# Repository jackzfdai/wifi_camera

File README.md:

# wifi_camera
ESP32 based connected camera, includes PCB files, ESP32 code, and a Python server for receiving the video stream.

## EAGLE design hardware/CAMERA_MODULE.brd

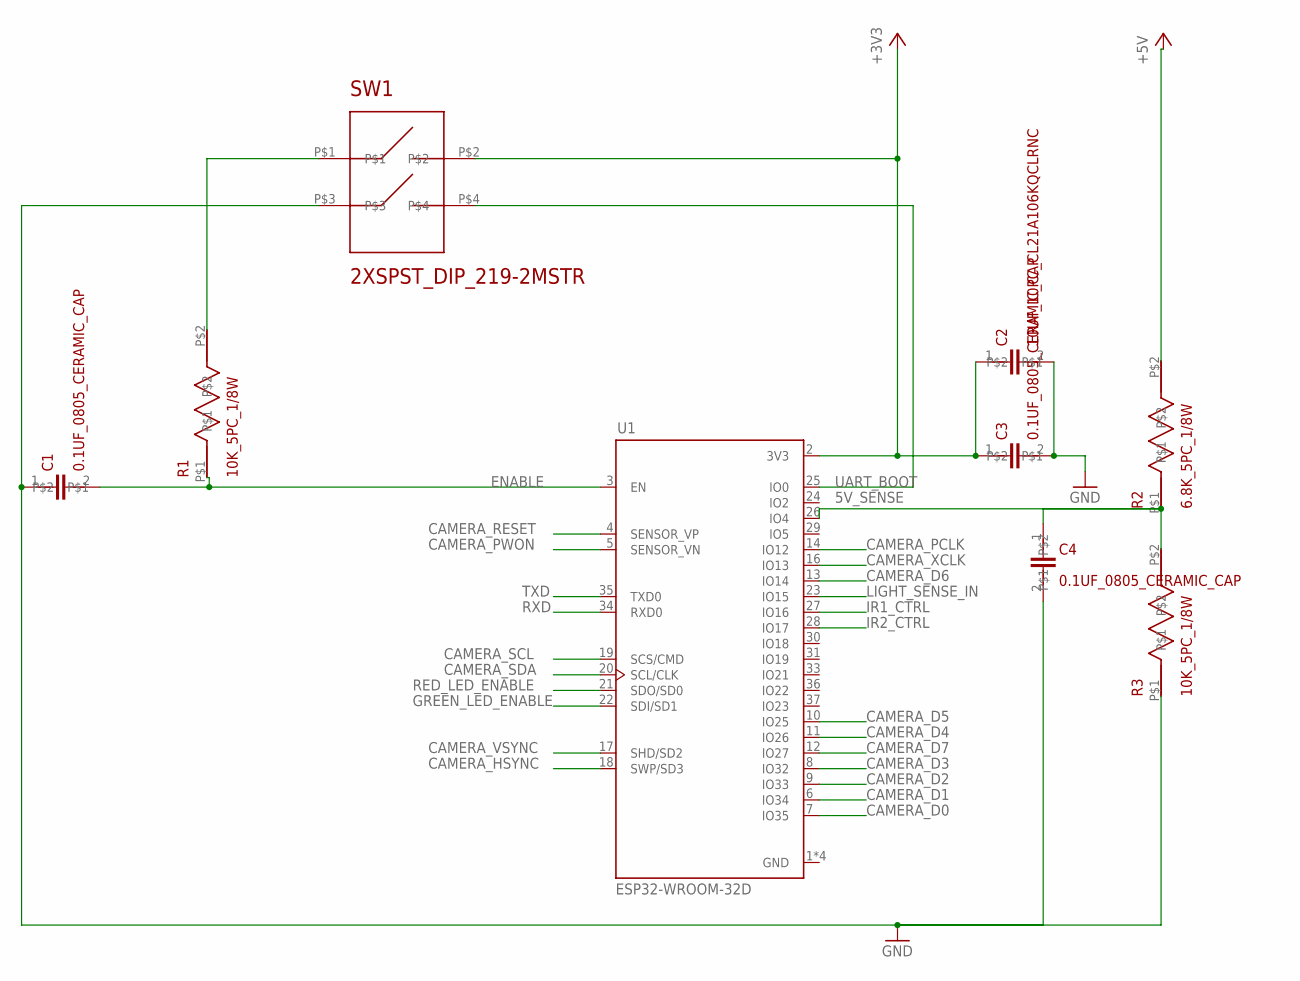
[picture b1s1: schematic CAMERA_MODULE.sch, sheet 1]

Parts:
C1, C3, C4: 0.1UF_0805_CERAMIC_CAP; C0805K
C2: 10UF_10PC_CL21A106KQCLRNC; C0805K
R1, R3: 10K_5PC_1/8W; 0805_1
R2: 6.8K_5PC_1/8W; 0805_1
SW1: 2XSPST_DIP_219-2MSTR; 2XSPST
U1: ESP32-WROOM-32D; MODULE_ESP32-WROOM-32D

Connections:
5V_SENSE: C4.1, R2.P$1, R3.P$2, U1.26 (IO4)
+3V3: C2.1, C3.1, SW1.P$2, U1.2 (3V3); also elsewhere on the board
+5V: R2.P$2; also elsewhere on the board
CAMERA_D0: U1.7 (IO35); also elsewhere on the board
CAMERA_D1: U1.6 (IO34); also elsewhere on the board
CAMERA_D2: U1.9 (IO33); also elsewhere on the board
CAMERA_D3: U1.8 (IO32); also elsewhere on the board
CAMERA_D4: U1.11 (IO26); also elsewhere on the board
CAMERA_D5: U1.10 (IO25); also elsewhere on the board
CAMERA_D6: U1.13 (IO14); also elsewhere on the board
CAMERA_D7: U1.12 (IO27); also elsewhere on the board
CAMERA_HSYNC: U1.18 (SWP/SD3); also elsewhere on the board
CAMERA_PCLK: U1.14 (IO12); also elsewhere on the board
CAMERA_PWON: U1.5 (SENSOR_VN); also elsewhere on the board
CAMERA_RESET: U1.4 (SENSOR_VP); also elsewhere on the board
CAMERA_SCL: U1.19 (SCS/CMD); also elsewhere on the board
CAMERA_SDA: U1.20 (SCL/CLK); also elsewhere on the board
CAMERA_VSYNC: U1.17 (SHD/SD2); also elsewhere on the board
CAMERA_XCLK: U1.16 (IO13); also elsewhere on the board
ENABLE: C1.2, R1.P$1, U1.3 (EN)
GND: C1.1, C2.2, C3.2, C4.2, R3.P$1, SW1.P$3, U1.1 (GND), U1.15 (GND), U1.38 (GND), U1.39 (GND); also elsewhere on the board
GREEN_LED_ENABLE: U1.22 (SDI/SD1); also elsewhere on the board
IR1_CTRL: U1.27 (IO16); also elsewhere on the board
IR2_CTRL: U1.28 (IO17); also elsewhere on the board
LIGHT_SENSE_IN: U1.23 (IO15); also elsewhere on the board
unnamed: R1.P$2, SW1.P$1
RED_LED_ENABLE: U1.21 (SDO/SD0); also elsewhere on the board
RXD: U1.34 (RXD0); also elsewhere on the board
TXD: U1.35 (TXD0); also elsewhere on the board
UART_BOOT: SW1.P$4, U1.25 (IO0)

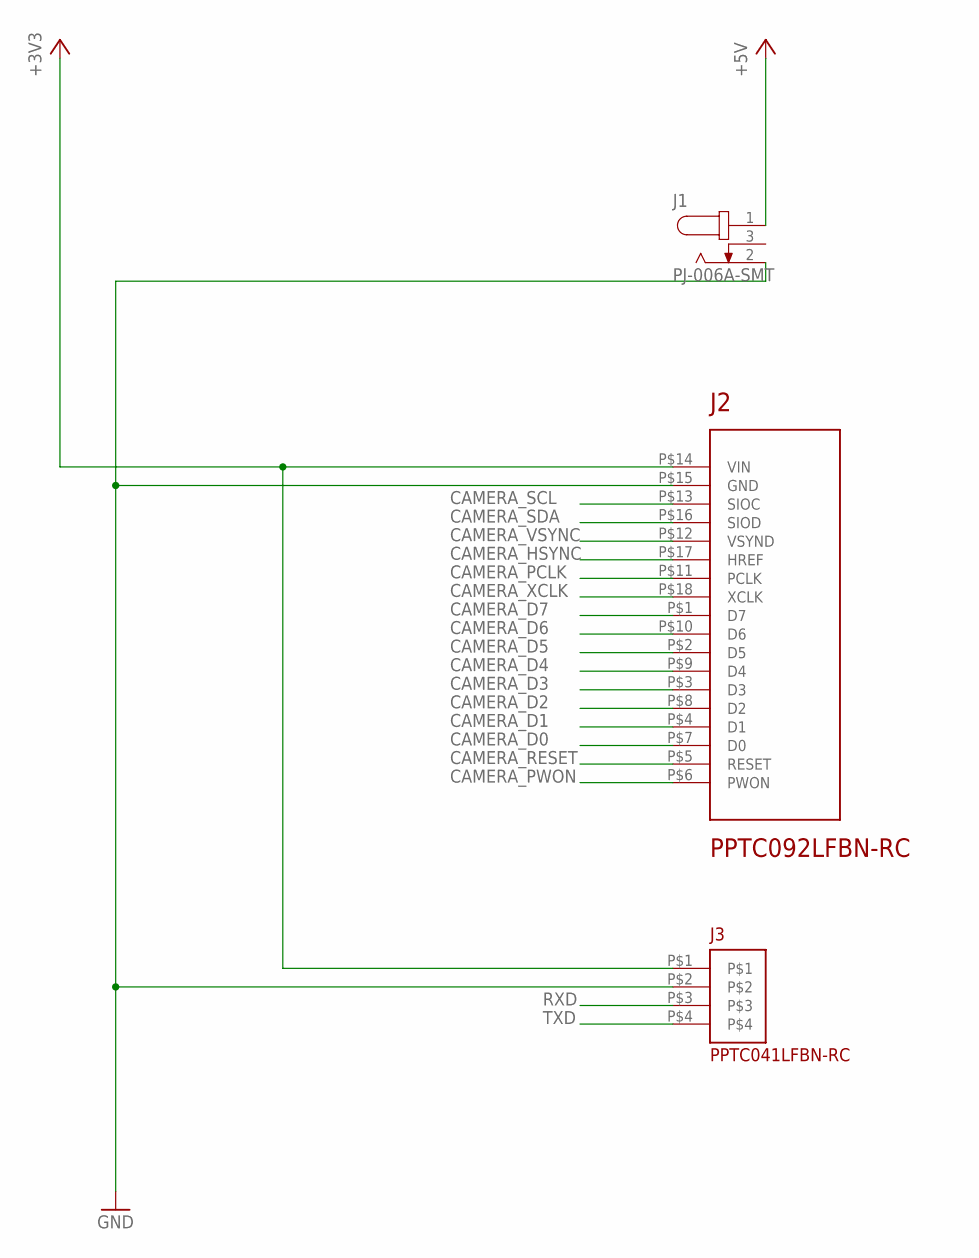
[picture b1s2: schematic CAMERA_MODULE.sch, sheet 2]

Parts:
J1: PJ-006A-SMT; CUI_PJ-006A-SMT
J2: PPTC092LFBN-RC; 2X9_0.1INCH
J3: PPTC041LFBN-RC; 1X4_0.1INCH

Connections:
+3V3: J2.P$14 (VIN), J3.P$1; also elsewhere on the board
+5V: J1.1; also elsewhere on the board
CAMERA_D0: J2.P$7 (D0); also elsewhere on the board
CAMERA_D1: J2.P$4 (D1); also elsewhere on the board
CAMERA_D2: J2.P$8 (D2); also elsewhere on the board
CAMERA_D3: J2.P$3 (D3); also elsewhere on the board
CAMERA_D4: J2.P$9 (D4); also elsewhere on the board
CAMERA_D5: J2.P$2 (D5); also elsewhere on the board
CAMERA_D6: J2.P$10 (D6); also elsewhere on the board
CAMERA_D7: J2.P$1 (D7); also elsewhere on the board
CAMERA_HSYNC: J2.P$17 (HREF); also elsewhere on the board
CAMERA_PCLK: J2.P$11 (PCLK); also elsewhere on the board
CAMERA_PWON: J2.P$6 (PWON); also elsewhere on the board
CAMERA_RESET: J2.P$5 (RESET); also elsewhere on the board
CAMERA_SCL: J2.P$13 (SIOC); also elsewhere on the board
CAMERA_SDA: J2.P$16 (SIOD); also elsewhere on the board
CAMERA_VSYNC: J2.P$12 (VSYND); also elsewhere on the board
CAMERA_XCLK: J2.P$18 (XCLK); also elsewhere on the board
GND: J1.2, J2.P$15 (GND), J3.P$2; also elsewhere on the board
RXD: J3.P$3; also elsewhere on the board
TXD: J3.P$4; also elsewhere on the board

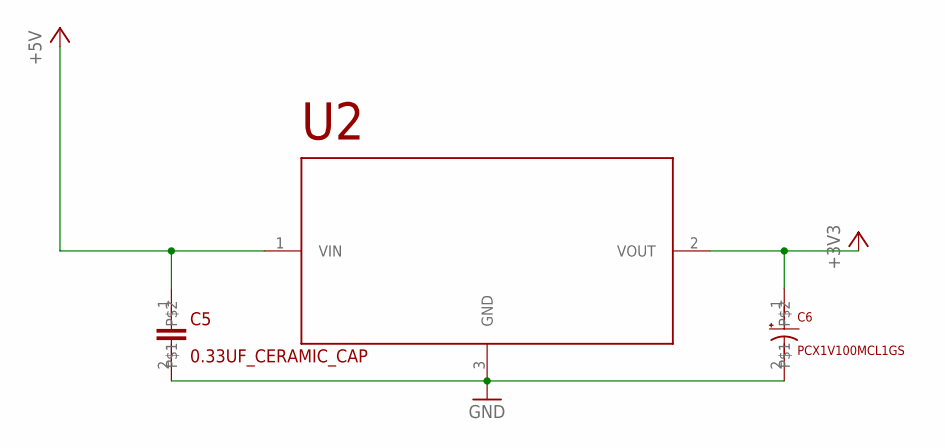
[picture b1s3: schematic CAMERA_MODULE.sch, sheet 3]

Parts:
C5: 0.33UF_CERAMIC_CAP; CAPC3216X110N
C6: PCX1V100MCL1GS; CAPAE660X600N
U2: LD29150DT33R; VREG_L7805CDT-TR

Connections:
+3V3: C6.1, U2.2 (VOUT); also elsewhere on the board
+5V: C5.1, U2.1 (VIN); also elsewhere on the board
GND: C5.2, C6.2, U2.3 (GND); also elsewhere on the board

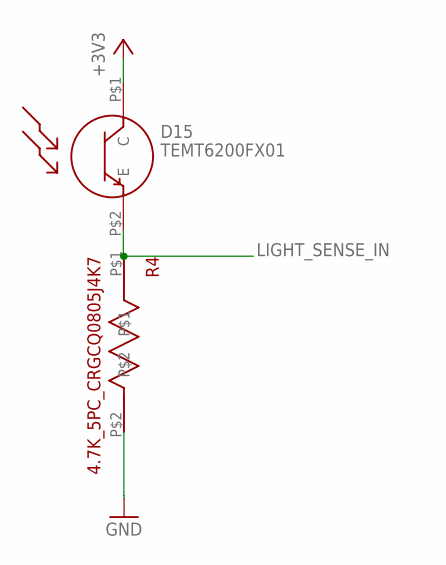
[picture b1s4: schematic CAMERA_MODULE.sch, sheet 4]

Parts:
D15: TEMT6200FX01; TEMT6200FX01_0805
R4: 4.7K_5PC_CRGCQ0805J4K7; 0805_1

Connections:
+3V3: D15.P$1 (C); also elsewhere on the board
GND: R4.P$2; also elsewhere on the board
LIGHT_SENSE_IN: D15.P$2 (E), R4.P$1; also elsewhere on the board

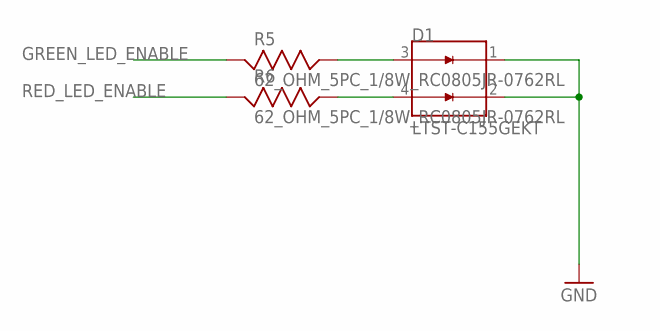
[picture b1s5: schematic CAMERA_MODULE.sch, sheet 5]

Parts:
D1: LTST-C155GEKT; LED_LTST-C155GEKT
R5, R6: 62_OHM_5PC_1/8W_RC0805JR-0762RL; 0805_1

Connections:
GND: D1.1, D1.2; also elsewhere on the board
GREEN_LED_ENABLE: R5.P$1 (1); also elsewhere on the board
unnamed: D1.3, R5.P$2 (2)
unnamed: D1.4, R6.P$2 (2)
RED_LED_ENABLE: R6.P$1 (1); also elsewhere on the board

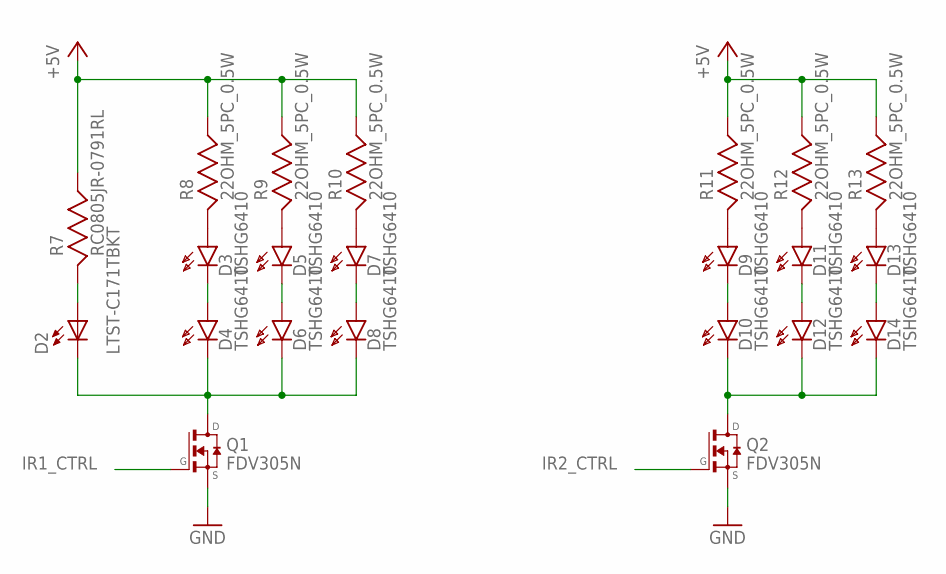
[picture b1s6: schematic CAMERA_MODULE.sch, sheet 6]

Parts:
D2: LTST-C171TBKT; DIOC200X125X110
D3, D4, D5, D6, D7, D8, D9, D10, D11, D12, D13, D14: TSHG6410; T1_LED_REAR_MOUNT
Q1, Q2: FDV305N; SOT23
R7: RC0805JR-0791RL; RESC2012X60
R8, R9, R10, R11, R12, R13: 22OHM_5PC_0.5W; 1206_RESISTOR

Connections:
+5V: R7.2, R8.P$2 (2), R9.P$2 (2), R10.P$2 (2), R11.P$2 (2), R12.P$2 (2), R13.P$2 (2); also elsewhere on the board
GND: Q1.2 (S), Q2.2 (S); also elsewhere on the board
IR1_CTRL: Q1.1 (G); also elsewhere on the board
IR2_CTRL: Q2.1 (G); also elsewhere on the board
unnamed: D2.+, R7.1
unnamed: D2.-, D4.P$2 (K), D6.P$2 (K), D8.P$2 (K), Q1.3 (D)
unnamed: D5.P$1 (A), R9.P$1 (1)
unnamed: D7.P$1 (A), R10.P$1 (1)
unnamed: D9.P$1 (A), R11.P$1 (1)
unnamed: D11.P$1 (A), R12.P$1 (1)
unnamed: D13.P$1 (A), R13.P$1 (1)
unnamed: D3.P$1 (A), R8.P$1 (1)
unnamed: D10.P$2 (K), D12.P$2 (K), D14.P$2 (K), Q2.3 (D)
unnamed: D3.P$2 (K), D4.P$1 (A)
unnamed: D5.P$2 (K), D6.P$1 (A)
unnamed: D7.P$2 (K), D8.P$1 (A)
unnamed: D9.P$2 (K), D10.P$1 (A)
unnamed: D11.P$2 (K), D12.P$1 (A)
unnamed: D13.P$2 (K), D14.P$1 (A)

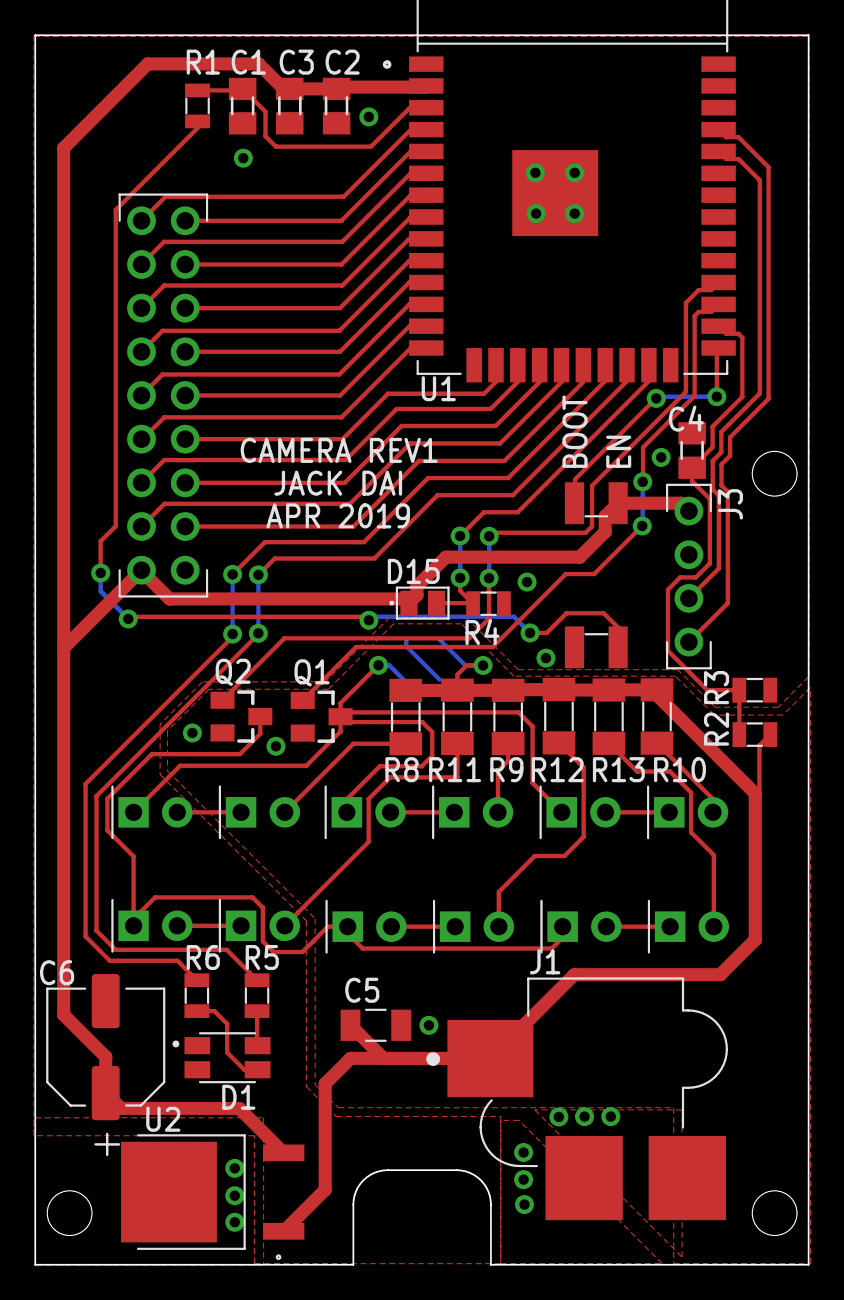
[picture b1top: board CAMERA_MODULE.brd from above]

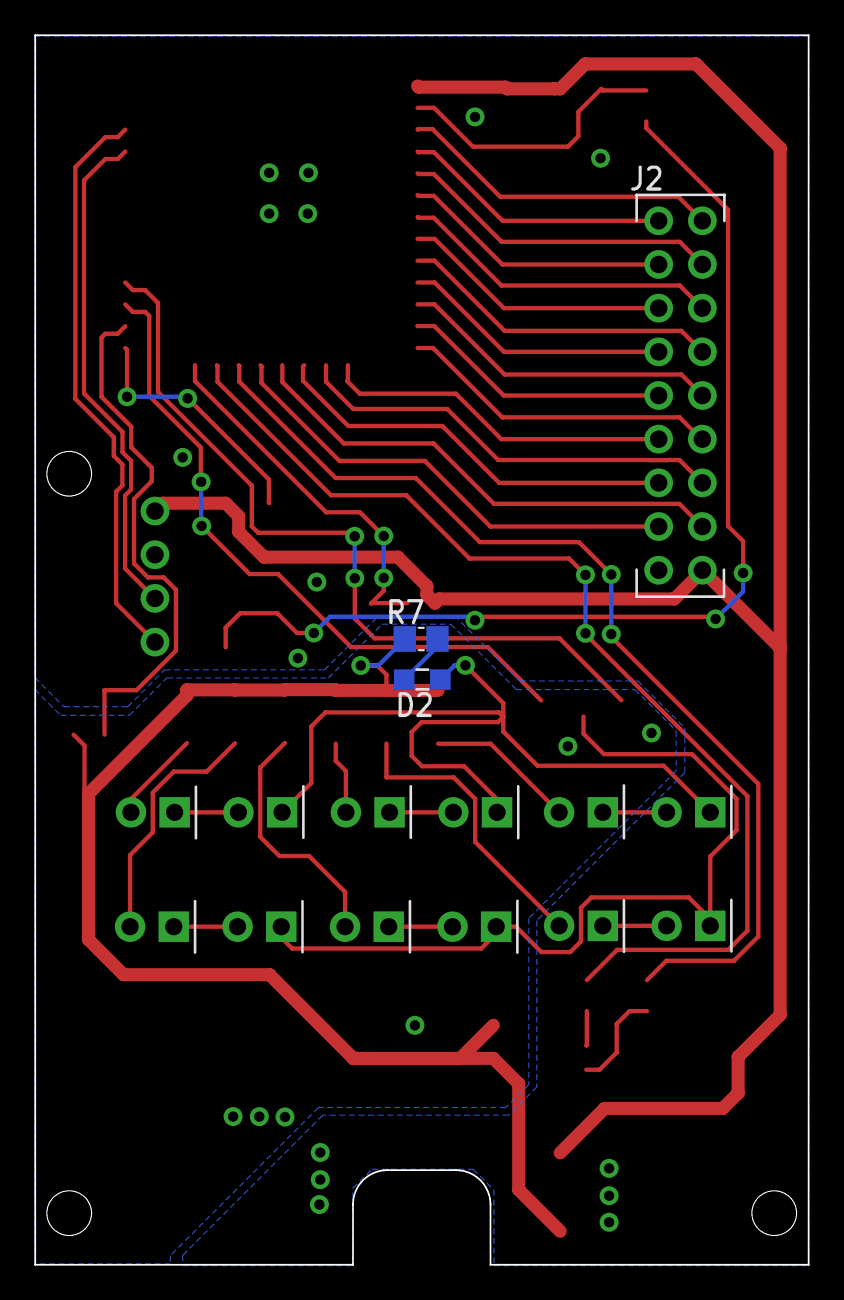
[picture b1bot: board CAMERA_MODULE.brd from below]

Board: 2 copper layers, 45.0 x 71.5 mm, 42 parts (2 on the bottom side), 47 nets.

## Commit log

2020-05-04 cleaned up git, ready to push to github. Working video compression and transfer. Working server prototype.
2020-05-04 added gitignore
2020-05-04 fixed bug in server code, improved frame rate w/ multiple frame buffers.
2020-05-05 working checkpoint, starting new branch for refactor
2020-05-06 added new state machine implementation for network module.
2020-05-06 debugged scrolling camera.
2020-05-07 working multiple jpeg buffers
2020-05-08 init network fsm w/o errors.
2020-05-08 added cmd recv to firmware.
2020-05-17 working client and server side client receive
2020-05-24 changed network protocol. Modifed python video client. python video client can now handle multiple web streams and send control frames to cameras.
2024-07-13 File cleanup.
